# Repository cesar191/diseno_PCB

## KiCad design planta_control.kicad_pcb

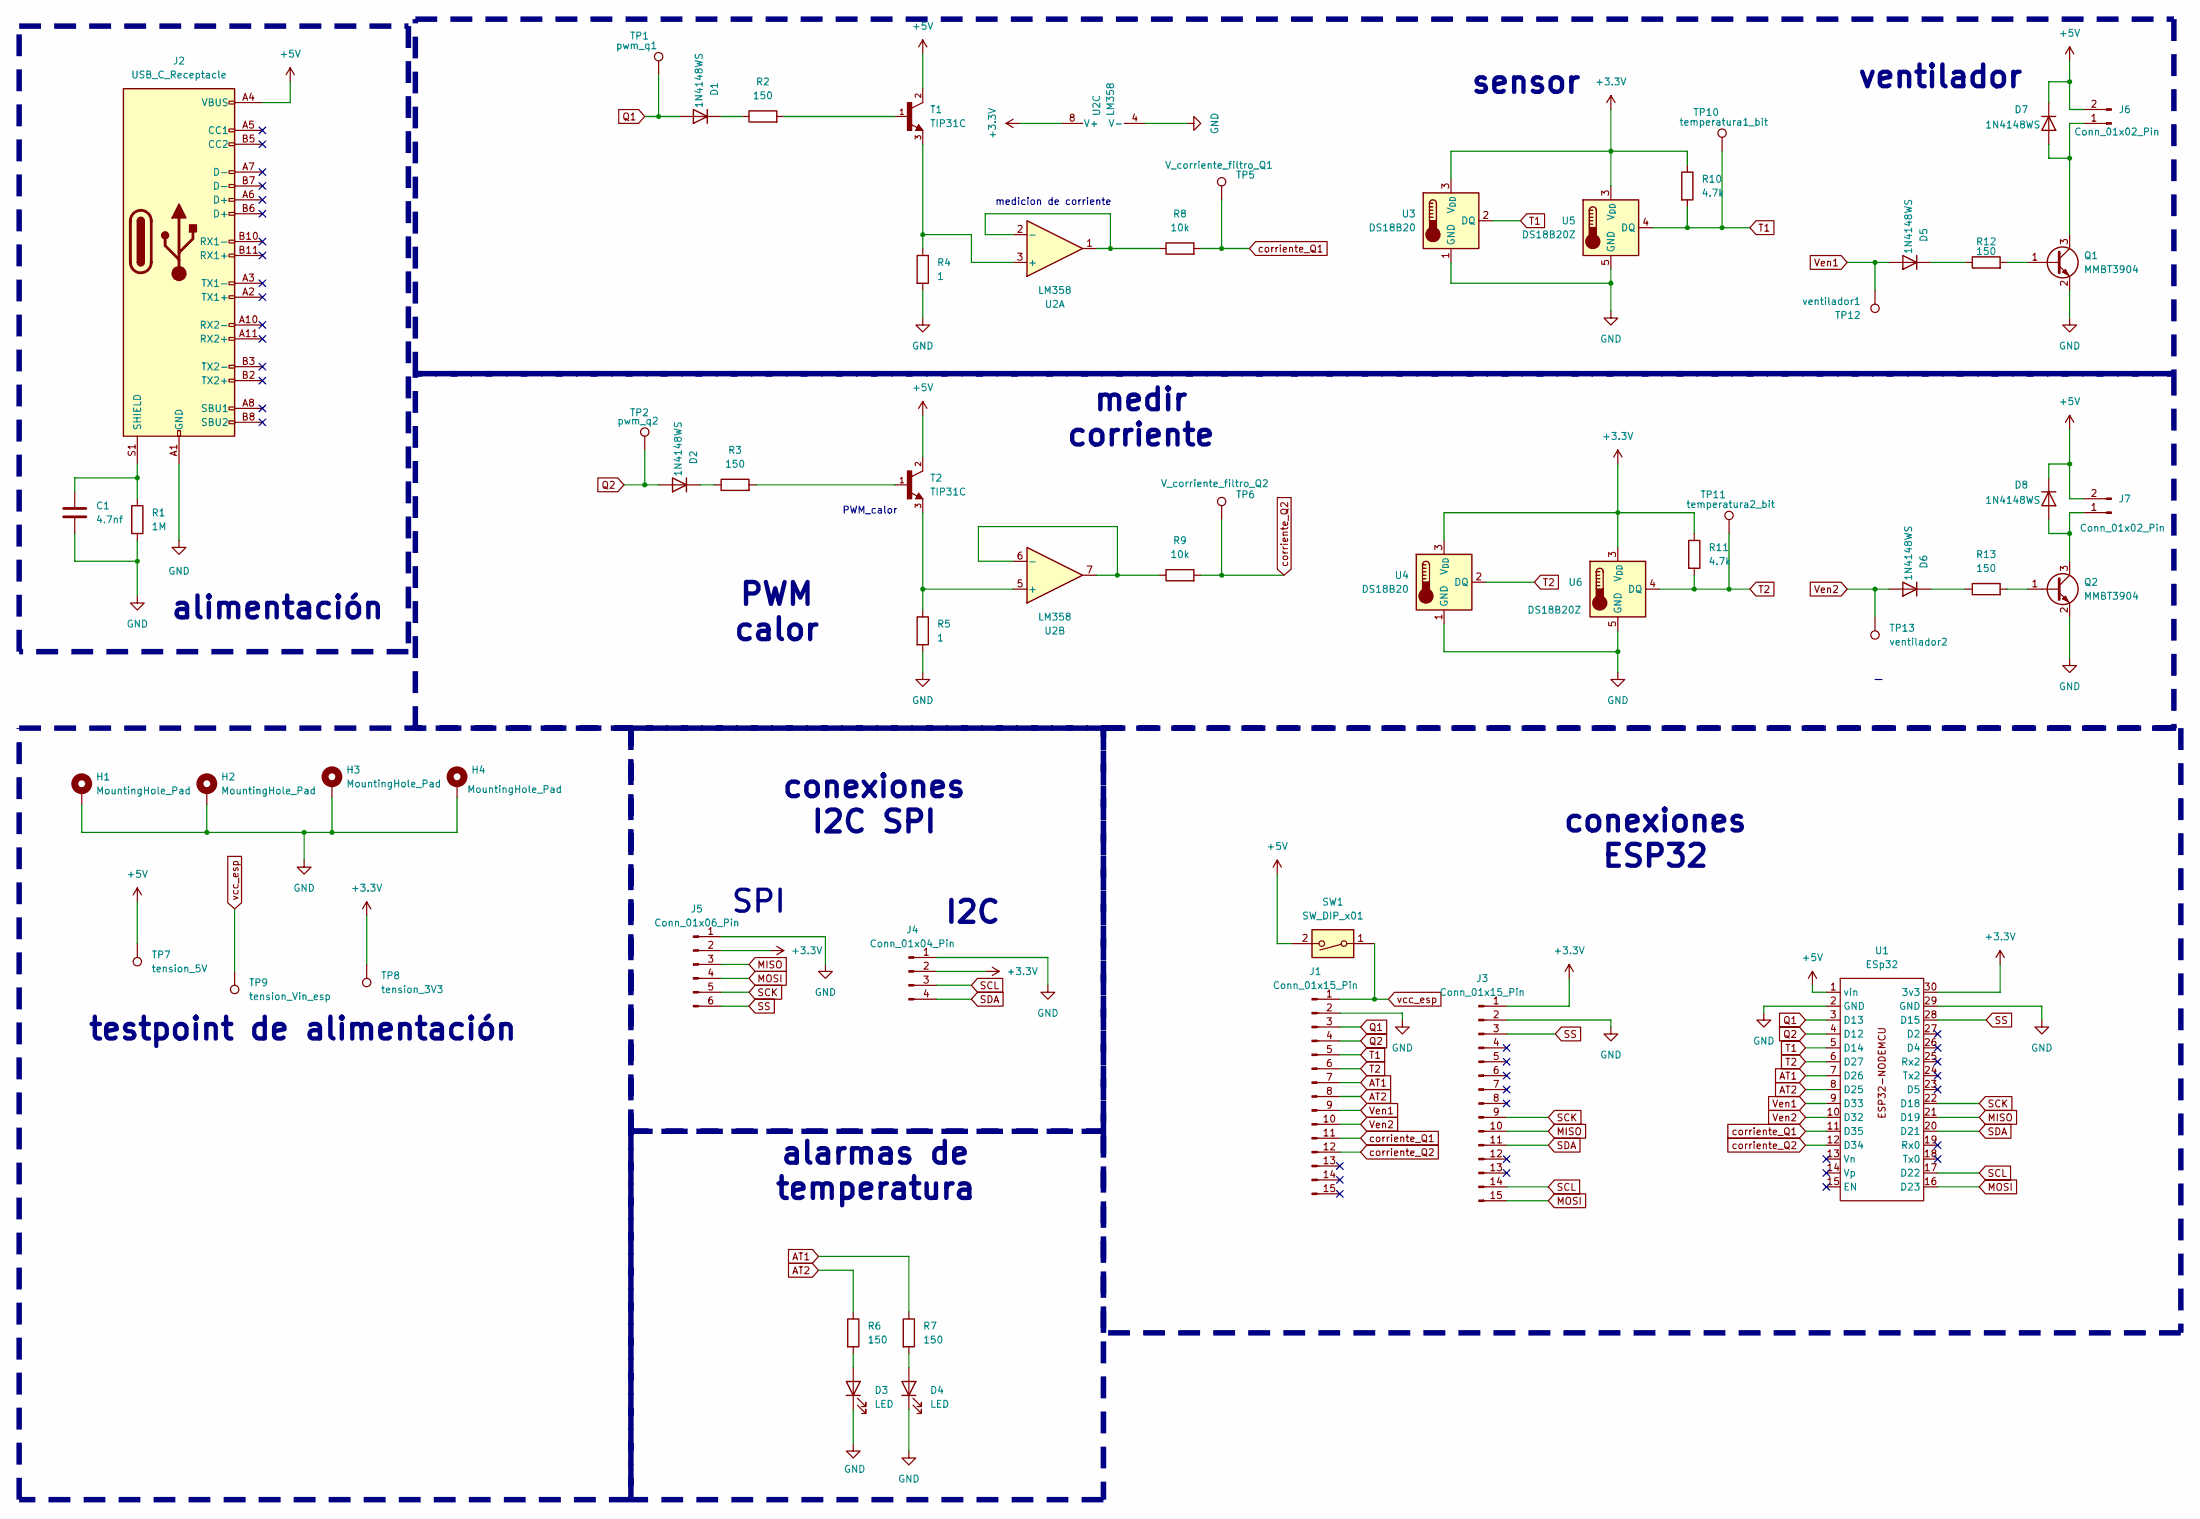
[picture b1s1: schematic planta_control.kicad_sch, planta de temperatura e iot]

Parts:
C1: 4.7nf; C_0805_2012Metric; JLCJLC C1744
D1, D2, D5, D6, D7, D8: 1N4148WS; D_SOD-323; JLCJLC C2128
D3, D4: LED; LED_0805_2012Metric; JLCJLC C84256
H1, H2, H3, H4: MountingHole_Pad; MountingHole_2.2mm_M2_Pad_Via
J1, J3: Conn_01x15_Pin; PinSocket_1x15_P2.54mm_Vertical
J2: USB_C_Receptacle; USB_C_Receptacle_Molex_105450-0101; JLCJLC C134092
J4: Conn_01x04_Pin; PinSocket_1x04_P2.54mm_Vertical
J5: Conn_01x06_Pin; PinSocket_1x06_P2.54mm_Vertical
J6, J7: Conn_01x02_Pin; PinHeader_1x02_P2.54mm_Vertical
Q1, Q2: MMBT3904; SOT-23; JLCJLC C20526
R1: 1M; R_0805_2012Metric; JLCJLC C17514
R2, R3, R6, R7, R12, R13: 150; R_0805_2012Metric; JLCJLC C17471
R4, R5: 1; R_2512_6332Metric; JLCJLC C11254
R8, R9: 10k; R_0805_2012Metric; JLCJLC C17414
R10, R11: 4.7k; R_0805_2012Metric; JLCJLC C17673
SW1: SW_DIP_x01; SW_DIP_SPSTx01_Slide_9.78x4.72mm_W7.62mm_P2.54mm
T1, T2: TIP31C; TO-220-3_Vertical; JLCJLC C13506
TP1: pwm_q1; TestPoint_THTPad_1.0x1.0mm_Drill0.5mm
TP2: pwm_q2; TestPoint_THTPad_1.0x1.0mm_Drill0.5mm
TP5: V_corriente_filtro_Q1; TestPoint_THTPad_1.0x1.0mm_Drill0.5mm
TP6: V_corriente_filtro_Q2; TestPoint_THTPad_1.0x1.0mm_Drill0.5mm
TP7: tension_5V; TestPoint_THTPad_1.0x1.0mm_Drill0.5mm
TP8: tension_3V3; TestPoint_THTPad_1.0x1.0mm_Drill0.5mm
TP9: tension_Vin_esp; TestPoint_THTPad_1.0x1.0mm_Drill0.5mm
TP10: temperatura1_bit; TestPoint_THTPad_1.0x1.0mm_Drill0.5mm
TP11: temperatura2_bit; TestPoint_THTPad_1.0x1.0mm_Drill0.5mm
TP12: ventilador1; TestPoint_THTPad_1.0x1.0mm_Drill0.5mm
TP13: ventilador2; TestPoint_THTPad_1.0x1.0mm_Drill0.5mm
U1: ESp32; ESP32_Node_MCU_30_Pines_2.5mm
U2: LM358; SOIC-8_5.3x6.2mm_P1.27mm; JLCJLC C7950
U3, U4: DS18B20; TO-92_Inline; JLCJLC C9753
U5, U6: DS18B20Z; SOIC-8_3.9x4.9mm_P1.27mm; JLCJLC C97190

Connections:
+5V: D7.1 (K), D8.1 (K), J2.A4 (VBUS), J2.A9 (VBUS), J2.B4 (VBUS), J2.B9 (VBUS), J6.2, J7.2, SW1.2, T1.2, T2.2, TP7.1 (1_1), U1.1 (vin)
AT1/D26: J1.7, R7.1, U1.7 (D26)
AT2/D25: J1.8, R6.1, U1.8 (D25)
GND: C1.2, D3.1 (K), D4.1 (K), H1.1 (1_1), H2.1 (1_1), H3.1 (1_1), H4.1 (1_1), J1.2, J2.A1 (GND), J2.A12 (GND), J2.B1 (GND), J2.B12 (GND), J3.2, J4.1, J5.1, Q1.2 (E), Q2.2 (E), R1.2, R4.2, R5.2, U1.2 (GND), U1.29 (GND), U2.4 (V-), U3.1 (GND), U4.1 (GND), U5.5 (GND), U6.5 (GND)
MISO/D19: J3.10, J5.3, U1.21 (D19)
MOSI/D23: J3.15, J5.4, U1.16 (D23)
unnamed: D1.1 (K), R2.1
unnamed: D2.1 (K), R3.1
unnamed: D3.2 (A), R6.2
unnamed: D4.2 (A), R7.2
unnamed: D5.1 (K), R12.1
unnamed: D6.1 (K), R13.1
unnamed: D7.2 (A), J6.1, Q1.3 (C)
unnamed: D8.2 (A), J7.1, Q2.3 (C)
unnamed: C1.1, J2.S1 (SHIELD), R1.1
unnamed: Q1.1 (B), R12.2
unnamed: Q2.1 (B), R13.2
unnamed: R2.2, T1.1
unnamed: R3.2, T2.1
unnamed: R4.1, T1.3, U2.3 (+)
unnamed: R8.1, U2.1, U2.2 (-)
unnamed: R5.1, T2.3, U2.5 (+)
unnamed: R9.1, U2.6 (-), U2.7
Q1/D13: D1.2 (A), J1.3, TP1.1 (1_1), U1.3 (D13)
Q2/D12: D2.2 (A), J1.4, TP2.1 (1_1), U1.4 (D12)
SCK/D18: J3.9, J5.5, U1.22 (D18)
SCL/D22: J3.14, J4.3, U1.17 (D22)
SDA/D21: J3.11, J4.4, U1.20 (D21)
SS/D15: J3.3, J5.6, U1.28 (D15)
T1/D14: J1.5, R10.2, TP10.1 (1_1), U1.5 (D14), U3.2 (DQ), U5.4 (DQ)
T2/D27: J1.6, R11.2, TP11.1 (1_1), U1.6 (D27), U4.2 (DQ), U6.4 (DQ)
Ven1/D33: D5.2 (A), J1.9, TP12.1 (1_1), U1.9 (D33)
Ven2/D32: D6.2 (A), J1.10, TP13.1 (1_1), U1.10 (D32)
corriente_Q1/D35: J1.11, R8.2, TP5.1 (1_1), U1.11 (D35)
corriente_Q2/D34: J1.12, R9.2, TP6.1 (1_1), U1.12 (D34)

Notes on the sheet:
ventilador
medir corriente
sensor
medicion de corriente
PWM calor
conexiones ESP32
alimentación
conexiones I2C SPI
testpoint de alimentación
PWM_calor
I2C
alarmas de temperatura
SPI

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
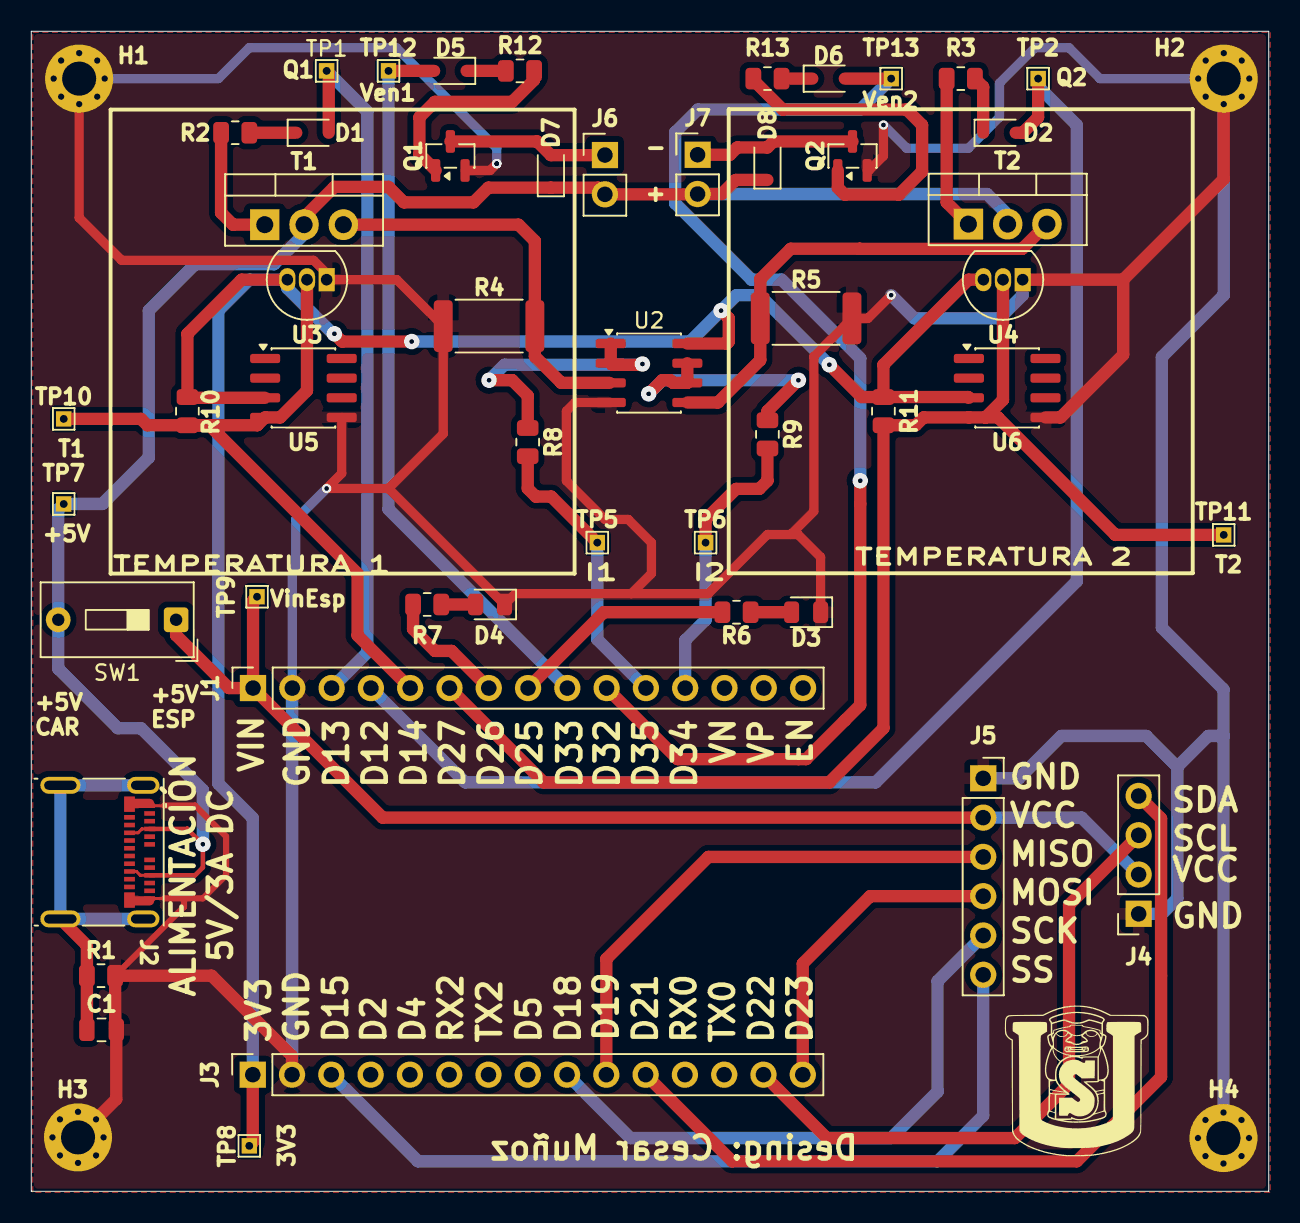
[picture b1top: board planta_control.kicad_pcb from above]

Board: 2 copper layers, 80.0 x 75.0 mm, 54 parts (0 on the bottom side), 37 nets.

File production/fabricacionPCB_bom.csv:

Designator,Footprint,Quantity,Value,LCSC Part #
C1,0805,1,4.7nf,C1744
"D1, D2, D5, D6, D7, D8",D_SOD-323,6,1N4148WS,C2128
"D3, D4",0805,2,LED,C84256
"J1, J3",PinSocket_1x15_P2.54mm_Vertical,2,Conn_01x15_Pin,
J2,USB_C_Receptacle_Molex_105450-0101,1,USB_C_Receptacle,C134092
J4,PinSocket_1x04_P2.54mm_Vertical,1,Conn_01x04_Pin,
J5,PinSocket_1x06_P2.54mm_Vertical,1,Conn_01x06_Pin,
"J6, J7",PinHeader_1x02_P2.54mm_Vertical,2,Conn_01x02_Pin,
"Q1, Q2",SOT-23,2,MMBT3904,C20526
R1,0805,1,1M,C17514
"R10, R11",0805,2,4.7k,C17673
"R12, R13, R2, R3, R6, R7",0805,6,150,C17471 
"R4, R5",2512,2,1,C11254
"R8, R9",0805,2,10k,C17414
SW1,SW_DIP_SPSTx01_Slide_9.78x4.72mm_W7.62mm_P2.54mm,1,SW_DIP_x01,
"T1, T2",TO-220-3_Vertical,2,TIP31C,C13506
TP1,TestPoint_THTPad_1.0x1.0mm_Drill0.5mm,1,pwm_q1,
TP10,TestPoint_THTPad_1.0x1.0mm_Drill0.5mm,1,temperatura1_bit,
TP11,TestPoint_THTPad_1.0x1.0mm_Drill0.5mm,1,temperatura2_bit,
TP12,TestPoint_THTPad_1.0x1.0mm_Drill0.5mm,1,ventilador1,
TP13,TestPoint_THTPad_1.0x1.0mm_Drill0.5mm,1,ventilador2,
TP2,TestPoint_THTPad_1.0x1.0mm_Drill0.5mm,1,pwm_q2,
TP5,TestPoint_THTPad_1.0x1.0mm_Drill0.5mm,1,V_corriente_filtro_Q1,
TP6,TestPoint_THTPad_1.0x1.0mm_Drill0.5mm,1,V_corriente_filtro_Q2,
TP7,TestPoint_THTPad_1.0x1.0mm_Drill0.5mm,1,tension_5V,
TP8,TestPoint_THTPad_1.0x1.0mm_Drill0.5mm,1,tension_3V3,
TP9,TestPoint_THTPad_1.0x1.0mm_Drill0.5mm,1,tension_Vin_esp,
U2,SOIC-8_5.3x6.2mm_P1.27mm,1,LM358,C7950
"U3, U4",TO-92_Inline,2,DS18B20,C9753
"U5, U6",SOIC-8_3.9x4.9mm_P1.27mm,2,DS18B20Z,C97190

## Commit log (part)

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2026-04-25 desing pcb v1.0.0
    diseño de la placa PCB en kicad
2026-04-25 .
    .
